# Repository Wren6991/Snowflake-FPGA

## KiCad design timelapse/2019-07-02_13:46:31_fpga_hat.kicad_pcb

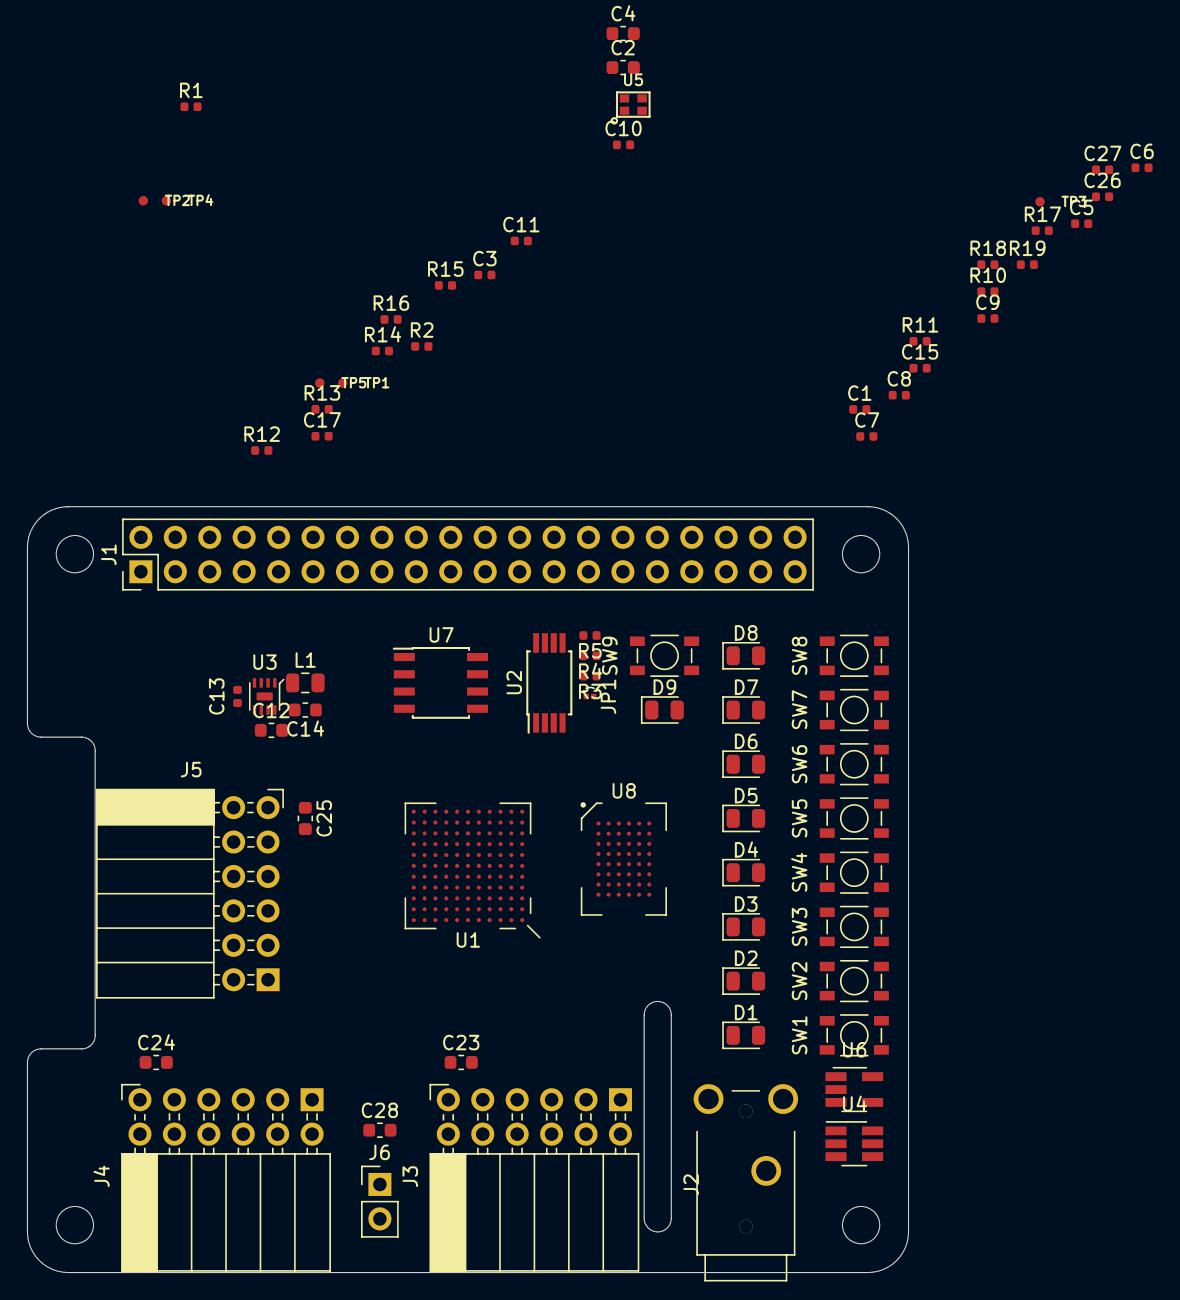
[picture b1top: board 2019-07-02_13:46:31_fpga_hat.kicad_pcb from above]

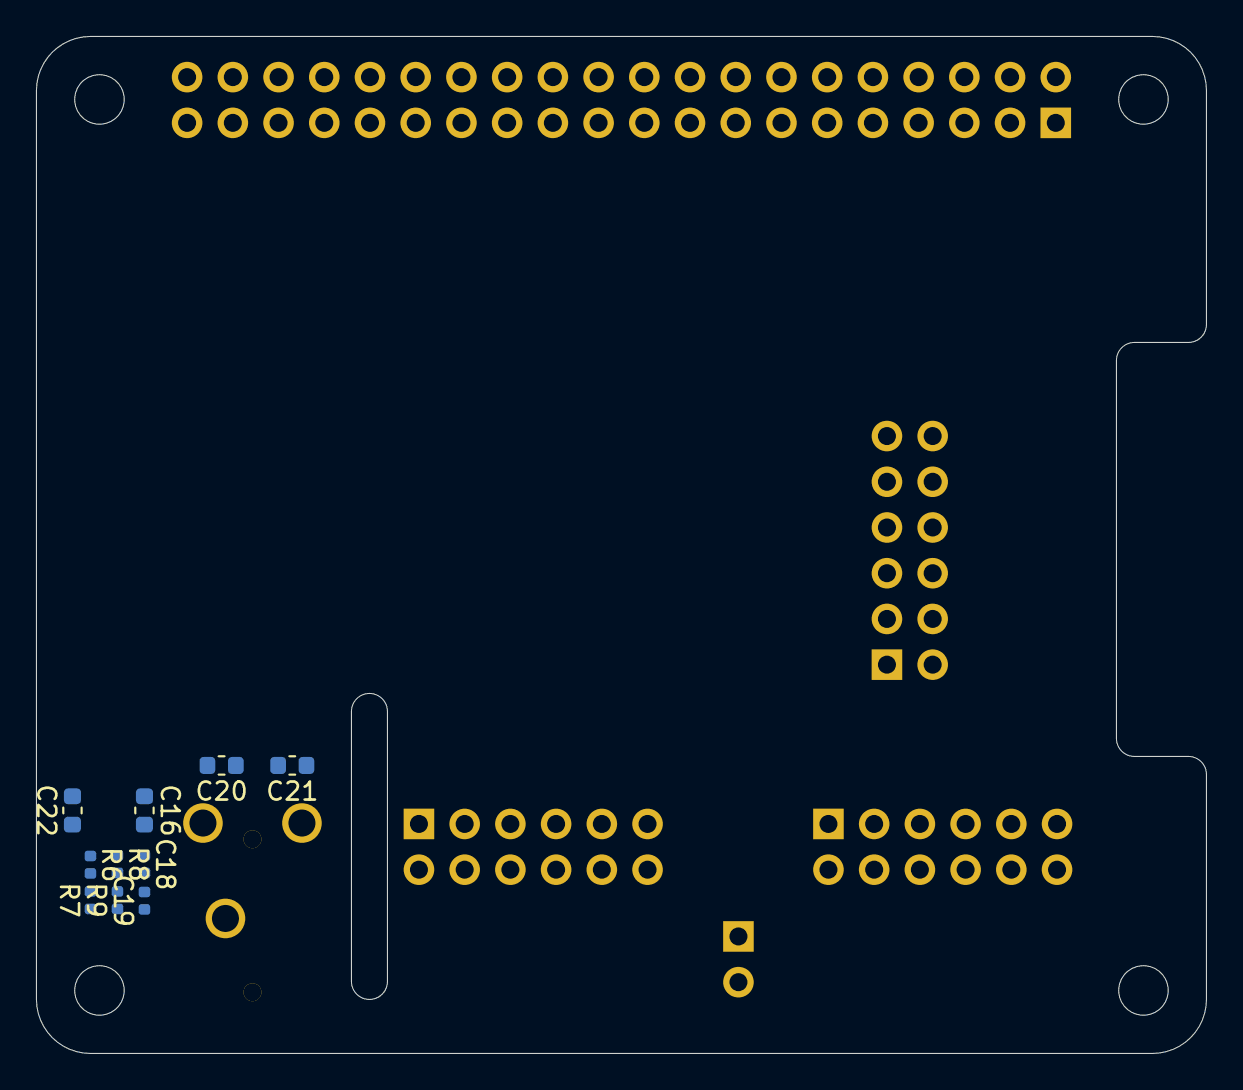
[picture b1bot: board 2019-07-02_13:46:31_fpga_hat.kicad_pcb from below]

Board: 4 copper layers, 65.0 x 56.5 mm, 86 parts (10 on the bottom side), 123 nets, no tracks yet.

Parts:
C1, C3, C5, C6, C7, C8, C9, C10, C11, C15, C17, C18, C19, C26, C27: 100n; C_0402_1005Metric
C2, C4, C12, C14, C20, C21: 4u7; C_0603_1608Metric
C13: 560p; C_0402_1005Metric
C16, C22, C23, C24, C25, C28: 1u; C_0603_1608Metric
D1, D2, D3, D4, D5, D6, D7, D8, D9: LED; LED_0805_2012Metric
J1: 2x20; PinHeader_2x20_P2.54mm_Vertical
J2: AudioJack3; STX-3000_TRS_3.5mm
J3, J4, J5: Conn_02x06_Top_Bottom; PinSocket_2x06_P2.54mm_Horizontal
J6: Conn_01x02; PinHeader_1x02_P2.54mm_Vertical
JP1: Solder jumper; SOLDER_JUMP
L1: 1u; L_0805_2012Metric
R1, R2, R8, R9: 100; R_0402_1005Metric
R3, R10, R11, R12, R13, R14, R15, R16, R17, R18: 470; R_0402_1005Metric
R4, R5, R19: 4k7; R_0402_1005Metric
R6, R7: 220; R_0402_1005Metric
SW1, SW2, SW3, SW4, SW5, SW6, SW7, SW8, SW9: PTS815
TP1, TP2, TP3, TP4, TP5: TestPoint; Testpoint_d0.7mm
U1: iCE40-HX8k-BG121; BGA-121_11x11_9.0x9.0mm
U2: CAT24C32WI; TSSOP-8_4.4x3mm_P0.65mm
U3: MIC23050-4YML; DFN8_2x2_0.5mm
U4: 74LVC2G07; SOT-23-6_Handsoldering
U5: DSC60XX; LGA4_1.6x1.2mm
U6: NCP115ASN330T; SOT-23-5_HandSoldering
U7: W25X40CL; SOIC-8_3.9x4.9mm_P1.27mm
U8: IS61WV25616; BGA-48_6x8_6.0x8.0mm

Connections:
+1V2: C1.1, C3.1, C5.1, C6.1, C13.1, C14.1, L1.2, R1.2, R2.2, TP2.1, U1.D4, U1.D8, U1.H4, U1.H8, U3.4
+3.3VDAC: C22.1, TP3.1, U4.5, U6.5
+3V3: C7.1, C8.1, C9.1, C10.1, C11.1, C15.1, C17.1, C23.1, C24.1, C25.1, C26.1, C27.1, J1.1, J1.17, J3.6, J3.12, J4.6, J4.12, J5.6, J5.12, R3.1, R4.1, R5.1, R18.2, R19.1, U1.C10, U1.D6, U1.E4, U1.F8, U1.G4, U1.H6, U1.L11, U2.8, U5.1, U5.4, U7.3, U7.7, U7.8, U8.D6, U8.E1
+5V: C12.1, C16.1, C28.1, J1.2, J1.4, J6.1, U3.2, U3.7, U6.1, U6.3
/AUDIO_L_PWM: U1.F11, U4.1
/AUDIO_R_PWM: U1.K7, U4.3
/CLK_OSC: U1.E10, U5.3
/GP8_SPI_~CS: J1.24, U1.K10, U7.1
/GP9_SPI_MISO: J1.21, U1.J9, U7.2
/GP10_SPI_MOSI: J1.19, U1.K9, U7.5
/GP11_SPI_SCK: J1.23, U1.L10, U7.6
/GP12_FPGA_~RST: J1.32, R19.2, SW9.1, TP5.1, U1.L9
/GP13_FPGA_CDONE: D9.2, J1.33, R18.1, TP4.1, U1.K8
/GP14_UART_TXD: J1.8, U1.C11
/GP15_UART_RXD: J1.10, U1.B11
/GP22_SDIO_CLK: J1.15, U1.J8
/GP23_SDIO_CMD: J1.16, U1.L7
/GP24_SDIO_DAT0: J1.18, U1.L8
/GP25_SDIO_DAT1: J1.22, U1.H9
/GP26_SDIO_DAT2: J1.37, U1.L5
/GP27_SDIO_DAT3: J1.13, U1.K6
/ID_SC: J1.28, R4.2, R5.2, U2.6
/ID_SD: J1.27, U2.5
/IO0_0: J3.1, U1.A11
/IO0_1: J3.2, U1.A10
/IO0_2: J3.3, U1.C9
/IO0_3: J3.4, U1.B9
/IO0_4: J3.7, U1.B8
/IO0_5: J3.8, U1.A9
/IO0_6: J3.9, U1.C8
/IO0_7: J3.10, U1.D7
/IO1_0: J4.1, U1.A8
/IO1_1: J4.2, U1.C7
/IO1_2: J4.3, U1.A7
/IO1_3: J4.4, U1.A6
/IO1_4: J4.7, U1.A5
/IO1_5: J4.8, U1.B5
/IO1_6: J4.9, U1.A4
/IO1_7: J4.10, U1.D5
/IO2_0: J5.1, U1.B4
/IO2_1: J5.2, U1.B3
/IO2_2: J5.3, U1.A2
/IO2_3: J5.4, U1.A3
/IO2_4: J5.7, U1.A1
/IO2_5: J5.8, U1.B7
/IO2_6: J5.9, U1.B6
/IO2_7: J5.10, U1.J11
/LED0: D1.2, U1.K11
/LED1: D2.2, U1.H10
/LED2: D3.2, U1.J10
/LED3: D4.2, U1.G8
/LED4: D5.2, U1.H11
/LED5: D6.2, U1.G10
/LED6: D7.2, U1.G9
/LED7: D8.2, U1.G11
/SRAM_A0: U1.G3, U8.A3
/SRAM_A1: U1.H3, U8.A4
/SRAM_A2: U1.H1, U8.A5
/SRAM_A3: U1.H2, U8.B3
/SRAM_A4: U1.J1, U8.B4
/SRAM_A5: U1.K1, U8.C3
/SRAM_A6: U1.K2, U8.C4
/SRAM_A7: U1.J2, U8.D4
/SRAM_A8: U1.F3, U8.H2
/SRAM_A9: U1.G1, U8.H3
/SRAM_A10: U1.L1, U8.H4
/SRAM_A11: U1.J3, U8.H5
/SRAM_A12: U1.L2, U8.G3
/SRAM_A13: U1.K3, U8.G4
/SRAM_A14: U1.J4, U8.F3
/SRAM_A15: U1.L3, U8.F4
/SRAM_A16: U1.L4, U8.E4
/SRAM_A17: U1.K4, U8.D3
/SRAM_DQ0: U1.B1, U8.B6
/SRAM_DQ1: U1.B2, U8.C5
/SRAM_DQ2: U1.C4, U8.C6
/SRAM_DQ3: U1.C3, U8.D5
/SRAM_DQ4: U1.C2, U8.E5
/SRAM_DQ5: U1.C1, U8.F5
/SRAM_DQ6: U1.E1, U8.F6
/SRAM_DQ7: U1.D1, U8.G6
/SRAM_DQ8: U1.D2, U8.B1
/SRAM_DQ9: U1.D3, U8.C1
/SRAM_DQ10: U1.E2, U8.C2
/SRAM_DQ11: U1.E3, U8.D2
/SRAM_DQ12: U1.F1, U8.E2
/SRAM_DQ13: U1.F2, U8.F2
/SRAM_DQ14: U1.F4, U8.F1
/SRAM_DQ15: U1.G2, U8.G1
/SRAM_~LB: U1.H7, U8.A1
/SRAM_~OE: U1.K5, U8.A2
/SRAM_~UB: U1.J7, U8.B2
/SRAM_~WE: U1.J5, U8.G5
/SW0: SW1.1, U1.F10
/SW1: SW2.1, U1.F9
/SW2: SW3.1, U1.E9
/SW3: SW4.1, U1.E8
/SW4: SW5.1, U1.D9
/SW5: SW6.1, U1.E11
/SW6: SW7.1, U1.D11
/SW7: SW8.1, U1.D10
GND: C1.2, C3.2, C5.2, C6.2, C7.2, C8.2, C9.2, C10.2, C11.2, C12.2, C14.2, C15.2, C16.2, C17.2, C18.2, C19.2, C22.2, C23.2, C24.2, C25.2, C26.2, C27.2, C28.2, D9.1, J1.6, J1.9, J1.14, J1.20, J1.25, J1.30, J1.34, J1.39, J2.S, J3.5, J3.11, J4.5, J4.11, J5.5, J5.11, J6.2, JP1.2, R8.2, R9.2, R10.1, R11.1, R12.1, R13.1, R14.1, R15.1, R16.1, R17.1, SW1.2, SW2.2, SW3.2, SW4.2, SW5.2, SW6.2, SW7.2, SW8.2, SW9.2, U1.E5, U1.E6, U1.E7, U1.F5, U1.F6, U1.F7, U1.G5, U1.G6, U1.G7, U1.H5, U2.1, U2.2, U2.3, U2.4, U3.6, U3.8, U4.2, U5.2, U6.2, U7.4, U8.B5, U8.D1, U8.E6
unnamed: C2.1, R2.1, U1.J6
unnamed: C2.2, U1.L6
unnamed: C4.1, R1.1, U1.C6
unnamed: C4.2, U1.C5
unnamed: C13.2, U3.5
unnamed: C18.1, C20.2, R6.1, R8.1
unnamed: C19.1, C21.2, R7.1, R9.1
unnamed: C20.1, J2.T
unnamed: C21.1, J2.R
unnamed: D1.1, R10.2
unnamed: D2.1, R11.2
unnamed: D3.1, R12.2
unnamed: D4.1, R13.2
unnamed: D5.1, R14.2
unnamed: D6.1, R15.2
unnamed: D7.1, R16.2
unnamed: D8.1, R17.2
unnamed: JP1.1, R3.2, TP1.1, U2.7
unnamed: L1.1, U3.1
unnamed: R6.2, U4.6
unnamed: R7.2, U4.4
